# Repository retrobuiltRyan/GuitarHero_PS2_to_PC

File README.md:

# GuitarHero_PS2_to_PC
Replace the Guitar Hero PS2 Controller PCB with a drop-in USB HID adapter PCB. Uses Arduino Pro Micro as a generic USB HID device. 
Extra details on my youtube video: https://youtu.be/DkvGg6Z6r1o
Pinout follows Daemon Byte Arcade encoder. 
I did not get the whammy connected as it has an unusual range in the stock PS2 design.

Tested to fit this GH guitar model (for PS2)

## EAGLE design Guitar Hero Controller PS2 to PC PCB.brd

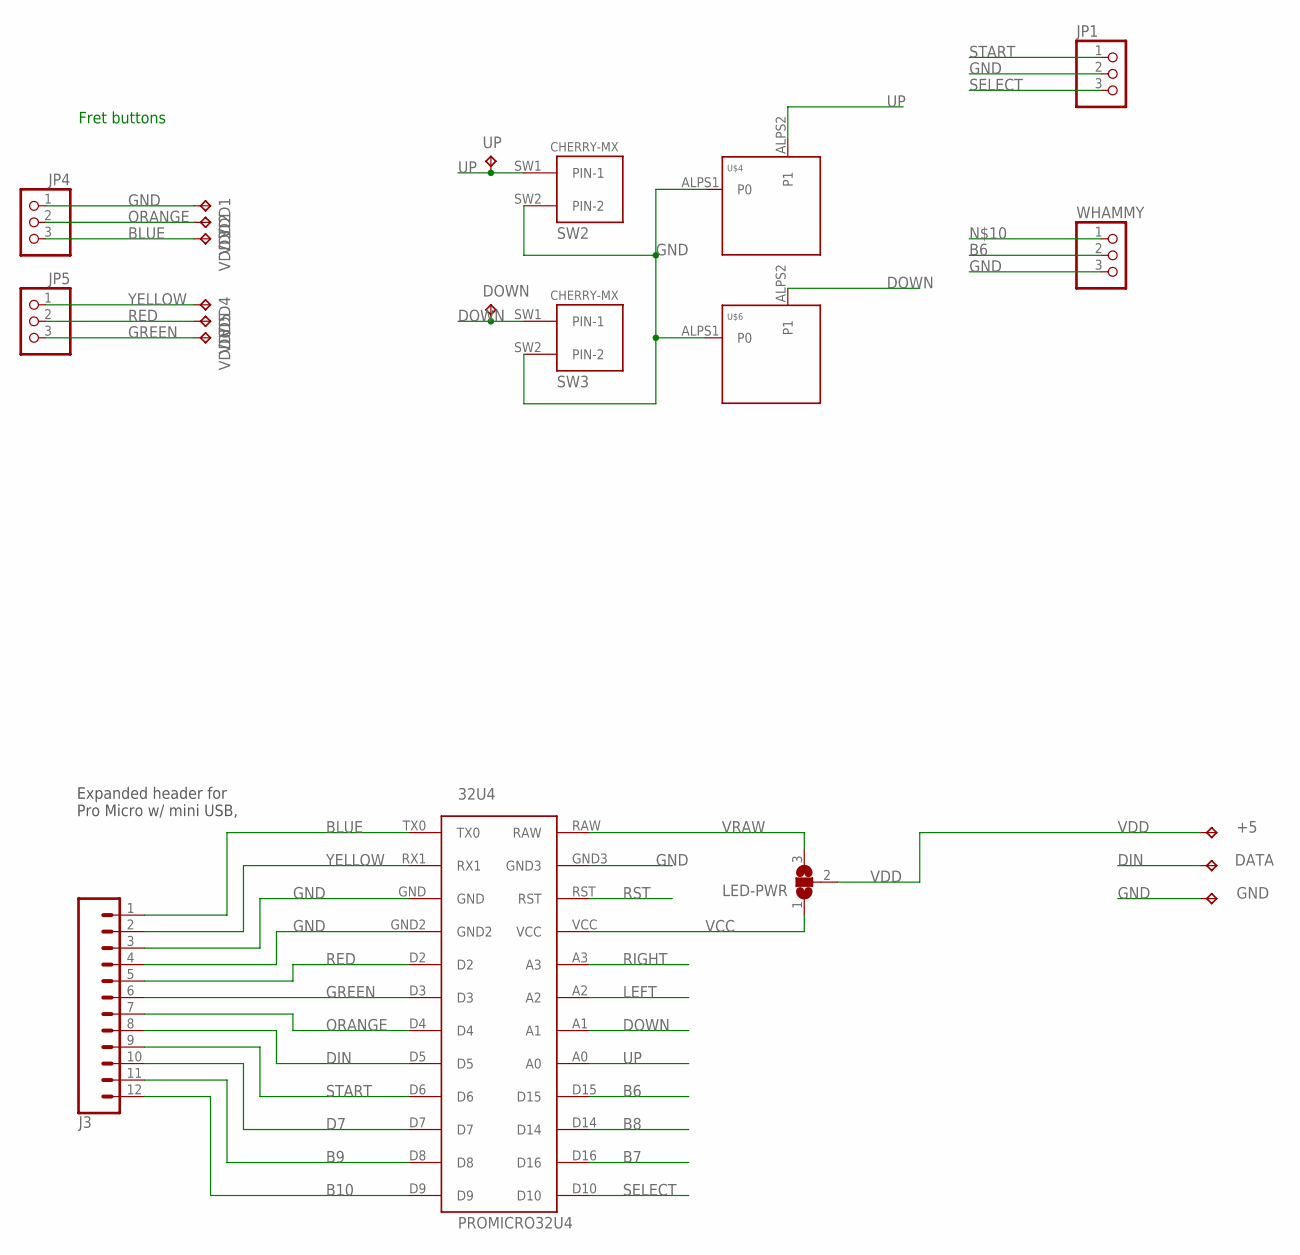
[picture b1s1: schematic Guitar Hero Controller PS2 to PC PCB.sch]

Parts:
32U4: PROMICRO32U4
+5: TPTP20SQ; TP20SQ
DATA: TPTP20SQ; TP20SQ
DOWN: TPTP20R; TP20R
GND: TPTP20SQ; TP20SQ
J3: CONN_12NO_SILK; 1X12_NO_SILK
JP1, JP4, JP5: PINHD-1X3CB; 1X03-CLEANBIG
LED-PWR: SJ2W; SJ_2
SW2, SW3: CHERRY-MX
U$4, U$6: KEYSWITCH-PLAIN-ALPS-1U; ALPS-1U
UP: TPTP20R; TP20R
VDD1, VDD2, VDD3, VDD4, VDD5, VDD6: TPTP20SQ; TP20SQ
WHAMMY: PINHD-1X3CB; 1X03-CLEANBIG

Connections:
B6: 32U4.D15, WHAMMY.2
B7: 32U4.D16
B8: 32U4.D14
B9: 32U4.D8, J3.11
B10: 32U4.D9, J3.12
BLUE: 32U4.TX0, J3.1, JP4.3, VDD3.TP
D7: 32U4.D7, J3.10
DIN: 32U4.D5, DATA.TP, J3.8
DOWN: 32U4.A1, DOWN.TP, SW3.SW1 (PIN-1), U$6.ALPS2 (P1)
GND: 32U4.GND, 32U4.GND2, 32U4.GND3, GND.TP, J3.3, J3.4, JP1.2, JP4.1, SW2.SW2 (PIN-2), SW3.SW2 (PIN-2), U$4.ALPS1 (P0), U$6.ALPS1 (P0), VDD1.TP, WHAMMY.3
GREEN: 32U4.D3, J3.6, JP5.3, VDD6.TP
LEFT: 32U4.A2
ORANGE: 32U4.D4, J3.7, JP4.2, VDD2.TP
RED: 32U4.D2, J3.5, JP5.2, VDD5.TP
RIGHT: 32U4.A3
RST: 32U4.RST
SELECT: 32U4.D10, JP1.3
START: 32U4.D6, J3.9, JP1.1
UP: 32U4.A0, SW2.SW1 (PIN-1), U$4.ALPS2 (P1), UP.TP
VCC: 32U4.VCC, LED-PWR.1
VDD: +5.TP, LED-PWR.2
VRAW: 32U4.RAW, LED-PWR.3
YELLOW: 32U4.RX1, J3.2, JP5.1, VDD4.TP

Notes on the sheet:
Fret buttons
Expanded header for Pro Micro w/ mini USB,

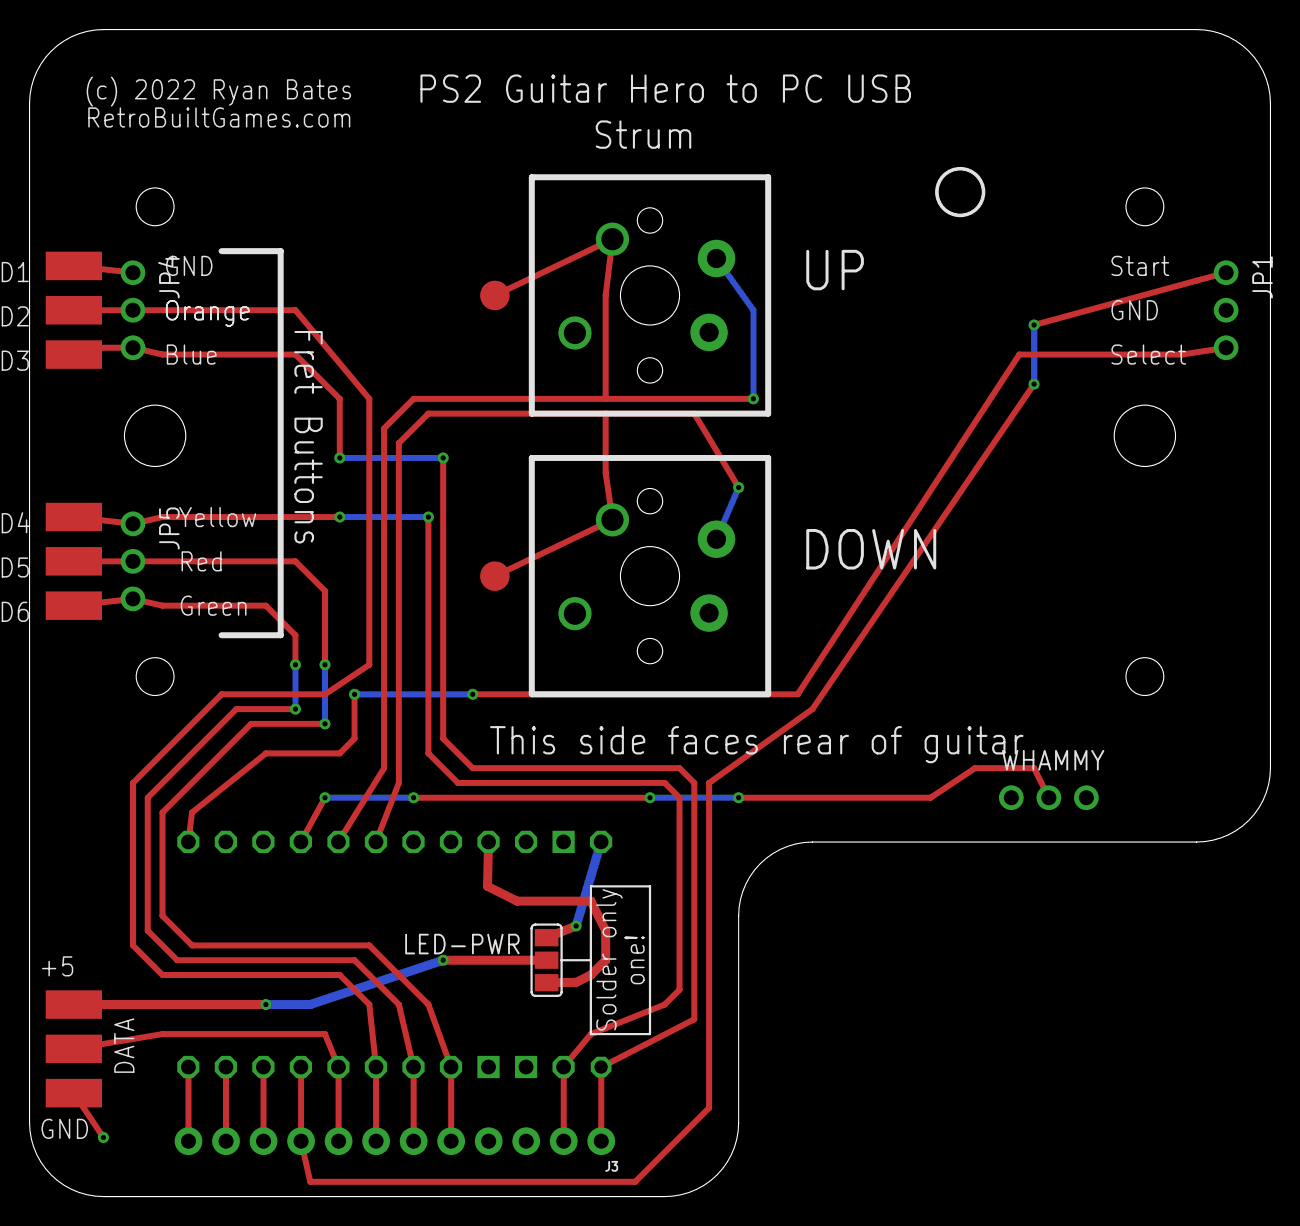
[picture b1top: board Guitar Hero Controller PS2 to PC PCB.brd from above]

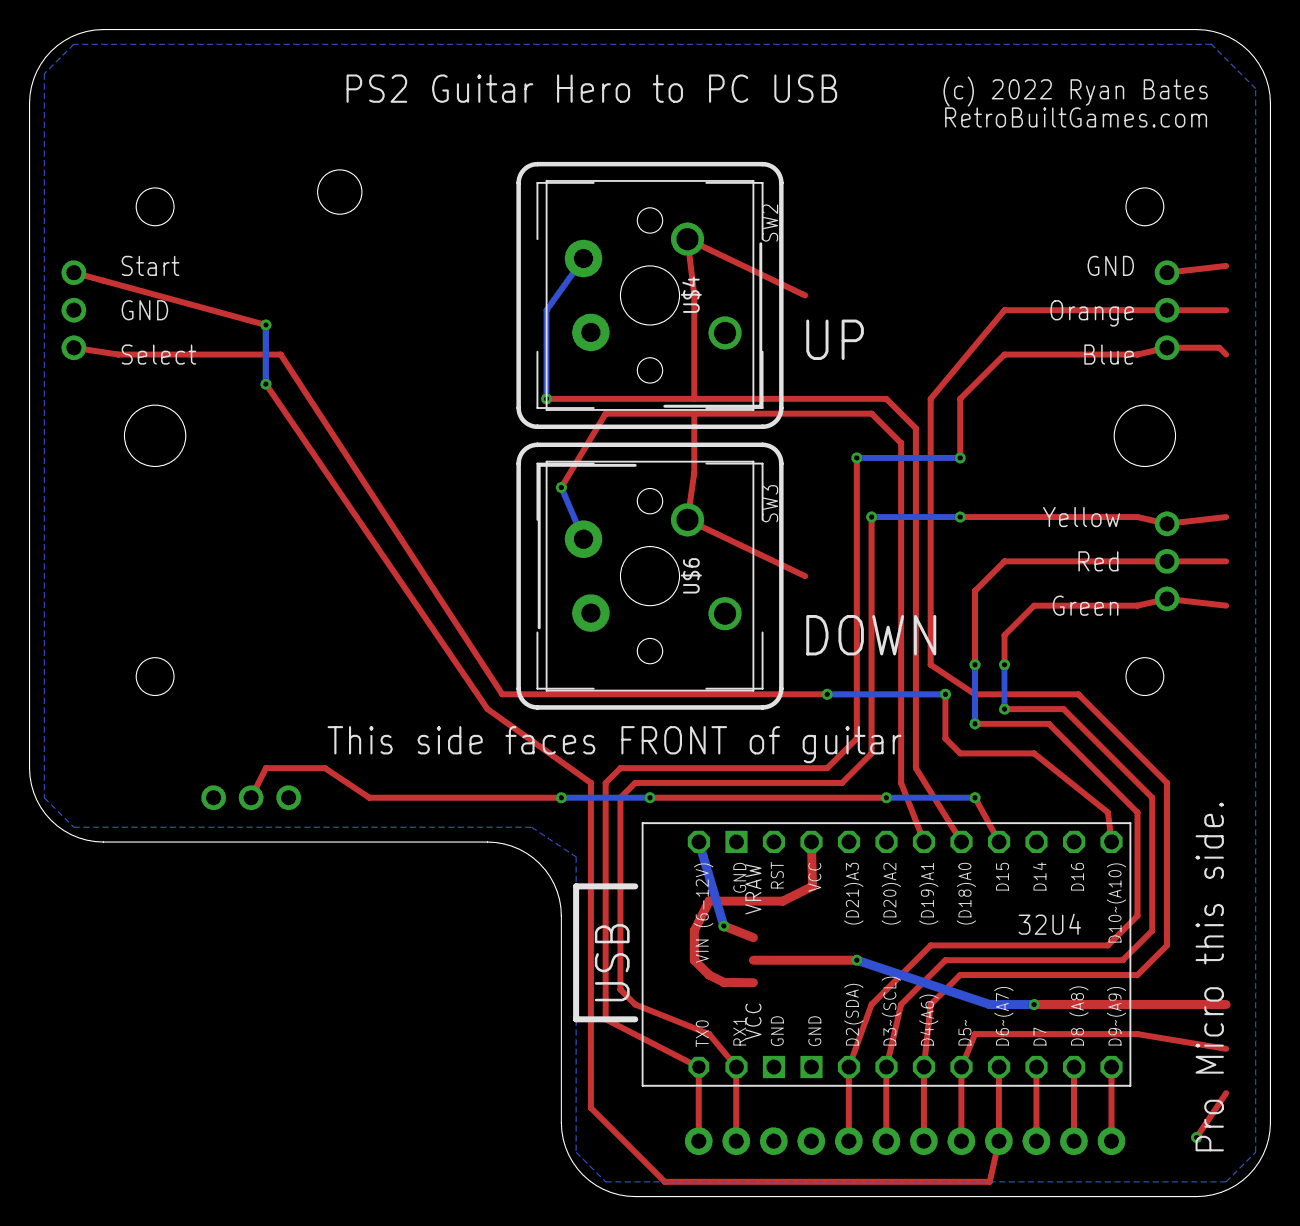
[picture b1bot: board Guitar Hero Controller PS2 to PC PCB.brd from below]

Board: 2 copper layers, 84.0 x 79.0 mm, 23 parts (5 on the bottom side), 18 nets.

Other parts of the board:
U$12: 3,0

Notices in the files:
Guitar Hero Controller PS2 to PC PCB.brd:
(c) 2022 Ryan Bates
parts and their libraries:
SparkFun-Connectors: Licensing: Creative Commons ShareAlike 4.0 International - https://creativecommons.org/licenses/by-sa/4.0
